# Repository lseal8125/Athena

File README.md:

THIS IS A WORK IN PROGRESS THE BOARD AND CODE HAS NOT BEEN FINISHED.
notes:
they way i want to have keymaps made and stored is in the code itself. after each keymap change the .uf2 will change making it so the code will have to be modified probably with some cli or better a gui. the reason for this is to allow many devices to plug in this keyboard and the key map will not change.

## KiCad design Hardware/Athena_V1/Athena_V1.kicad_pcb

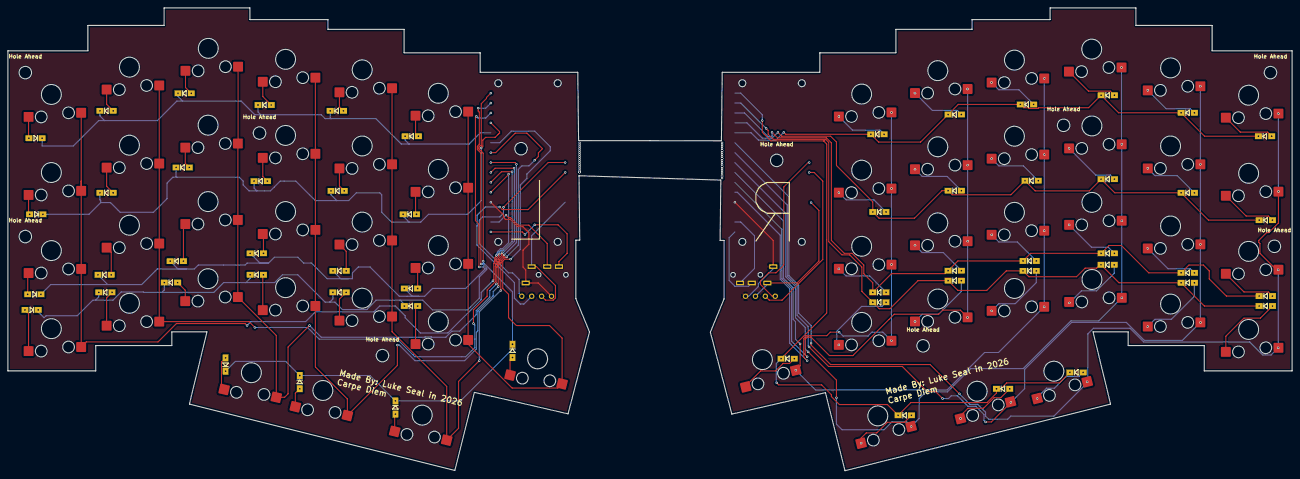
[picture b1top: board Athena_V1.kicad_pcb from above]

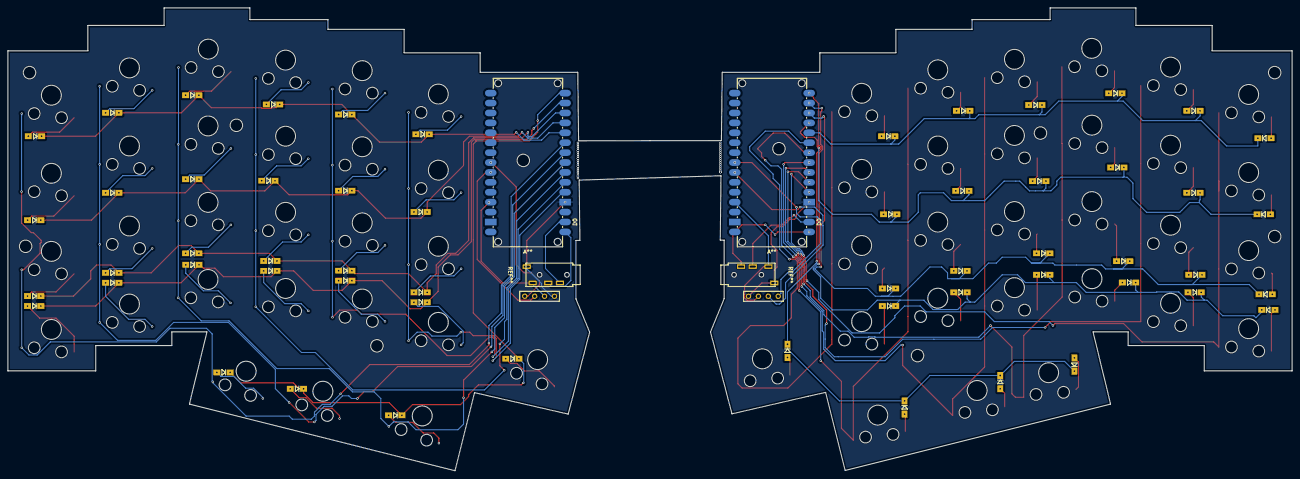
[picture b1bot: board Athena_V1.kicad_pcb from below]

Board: 2 copper layers, 329.0 x 118.6 mm, 126 parts (2 on the bottom side), 74 nets.

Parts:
A**: Arduino_Nano_Every_Tile
A**#2: Arduino_Nano_Every_Tile
D1, D2, D3, D4, D5, D6, D7, D8, D9, D10, D11, D12, D13, D14, D15, D16, D17, D18, D19, D20, D21, D22, D23, D24, D25, D26, D27, D28, D29, D30, D31, D32, D57, D58, D59, D60, D61, D62, D63, D64, D65, D66, D67, D68, D69, D70, D71, D72, D73, D74, D75, D76, D77, D78, D79, D80: D; Diode_SOD123
Hole Ahead: MountingHole_3.2mm_M3
Hole Ahead#2, Hole Ahead#3, Hole Ahead#4, Hole Ahead#5, Hole Ahead#6, Hole Ahead#7, Hole Ahead#8, Hole Ahead#9, Hole Ahead#10: MountingHole_3.2mm_M3
J3, J3#2: OLED; OLED_4Pin
SW1, SW2, SW3, SW4, SW5, SW6, SW7, SW8, SW9, SW10, SW11, SW12, SW13, SW14, SW15, SW16, SW17, SW18, SW19, SW20, SW21, SW22, SW23, SW24, SW25, SW26, SW27, SW28, SW29, SW30, SW31, SW32, SW57, SW58, SW59, SW60, SW61, SW62, SW63, SW64, SW65, SW66, SW67, SW68, SW69, SW70, SW71, SW72, SW73, SW74, SW75, SW76, SW77, SW78, SW79, SW80: SW_Push; Gateron-KS33-Hotswap-1U

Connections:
+5V: A**#2.5V, J3.2
+5VA: A**.5V, J3#2.3
COL0: A**.D2, A**#2.D2, SW5.1, SW6.1, SW7.1, SW8.1, SW57.1, SW58.1, SW59.1, SW64.1
COL1: A**.D3, A**#2.D3, SW9.1, SW10.1, SW11.1, SW12.1, SW60.1, SW61.1, SW62.1, SW63.1
COL2: A**.D4, A**#2.D4, SW1.1, SW13.1, SW14.1, SW15.1, SW16.1, SW17.1, SW65.1, SW66.1, SW67.1, SW68.1
COL3: A**.D5, A**#2.D5, SW2.1, SW18.1, SW19.1, SW20.1, SW21.1, SW22.1, SW69.1, SW70.1, SW71.1, SW72.1
COL4: A**.D6, A**#2.D6, SW3.1, SW23.1, SW24.1, SW25.1, SW26.1, SW27.1, SW73.1, SW74.1, SW75.1, SW76.1
COL5: A**.D7, A**#2.D7, SW4.1, SW28.1, SW29.1, SW30.1, SW31.1, SW32.1, SW77.1, SW78.1, SW79.1, SW80.1
GNDA: A**.GND1, A**#2.GND1, J3.1, J3#2.4
unnamed: D1.2 (A), SW1.2
unnamed: D2.2 (A), SW2.2
unnamed: D3.2 (A), SW3.2
unnamed: D4.2 (A), SW4.2
unnamed: D5.2 (A), SW5.2
unnamed: D6.2 (A), SW6.2
unnamed: D7.2 (A), SW7.2
unnamed: D8.2 (A), SW8.2
unnamed: D9.2 (A), SW9.2
unnamed: D10.2 (A), SW10.2
unnamed: D11.2 (A), SW11.2
unnamed: D12.2 (A), SW12.2
unnamed: D13.2 (A), SW13.2
unnamed: D14.2 (A), SW14.2
unnamed: D15.2 (A), SW15.2
unnamed: D16.2 (A), SW16.2
unnamed: D17.2 (A), SW17.2
unnamed: D18.2 (A), SW18.2
unnamed: D19.2 (A), SW19.2
unnamed: D20.2 (A), SW20.2
unnamed: D21.2 (A), SW21.2
unnamed: D22.2 (A), SW22.2
unnamed: D23.2 (A), SW23.2
unnamed: D24.2 (A), SW24.2
unnamed: D25.2 (A), SW25.2
unnamed: D26.2 (A), SW26.2
unnamed: D27.2 (A), SW27.2
unnamed: D28.2 (A), SW28.2
unnamed: D29.2 (A), SW29.2
unnamed: D30.2 (A), SW30.2
unnamed: D31.2 (A), SW31.2
unnamed: D32.2 (A), SW32.2
unnamed: D57.2 (A), SW57.2
unnamed: D58.2 (A), SW58.2
unnamed: D59.2 (A), SW59.2
unnamed: D60.2 (A), SW60.2
unnamed: D61.2 (A), SW61.2
unnamed: D62.2 (A), SW62.2
unnamed: D63.2 (A), SW63.2
unnamed: D64.2 (A), SW64.2
unnamed: D65.2 (A), SW65.2
unnamed: D66.2 (A), SW66.2
unnamed: D67.2 (A), SW67.2
unnamed: D68.2 (A), SW68.2
unnamed: D69.2 (A), SW69.2
unnamed: D70.2 (A), SW70.2
unnamed: D71.2 (A), SW71.2
unnamed: D72.2 (A), SW72.2
unnamed: D73.2 (A), SW73.2
unnamed: D74.2 (A), SW74.2
unnamed: D75.2 (A), SW75.2
unnamed: D76.2 (A), SW76.2
unnamed: D77.2 (A), SW77.2
unnamed: D78.2 (A), SW78.2
unnamed: D79.2 (A), SW79.2
unnamed: D80.2 (A), SW80.2
ROW0: A**.D8, A**#2.D8, D5.1 (K), D9.1 (K), D13.1 (K), D18.1 (K), D23.1 (K), D28.1 (K), D57.1 (K), D61.1 (K), D65.1 (K), D69.1 (K), D73.1 (K), D77.1 (K)
ROW1: A**.D9, A**#2.D9, D6.1 (K), D10.1 (K), D14.1 (K), D19.1 (K), D24.1 (K), D29.1 (K), D58.1 (K), D62.1 (K), D66.1 (K), D70.1 (K), D74.1 (K), D78.1 (K)
ROW2: A**.D10, A**#2.D10, D7.1 (K), D11.1 (K), D15.1 (K), D20.1 (K), D25.1 (K), D30.1 (K), D59.1 (K), D63.1 (K), D67.1 (K), D71.1 (K), D75.1 (K), D79.1 (K)
ROW3: A**.D11, A**#2.D11, D8.1 (K), D12.1 (K), D16.1 (K), D21.1 (K), D26.1 (K), D31.1 (K), D60.1 (K), D64.1 (K), D68.1 (K), D72.1 (K), D76.1 (K), D80.1 (K)
ROW4: A**.D12, A**#2.D12, D1.1 (K), D2.1 (K), D3.1 (K), D4.1 (K), D17.1 (K), D22.1 (K), D27.1 (K), D32.1 (K)
RX0: A**.D0, A**#2.D0
SCL: A**.A5, A**#2.A5, J3.3, J3#2.2
SDA: A**.A4, A**#2.A4, J3.4, J3#2.1
TX0: A**.D1, A**#2.D1

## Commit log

2026-02-05 init
2026-02-05 added board files
2026-02-05 Add README.md
2026-02-05 test code 1 made
    no bt, single side, no HID, simple serial out with col, row.
2026-02-12 Added Keyboard lib, worked on firmware structure
2026-04-22 Started Research
    Started research into usb hid to understand usb and the hid protocol from scratch
